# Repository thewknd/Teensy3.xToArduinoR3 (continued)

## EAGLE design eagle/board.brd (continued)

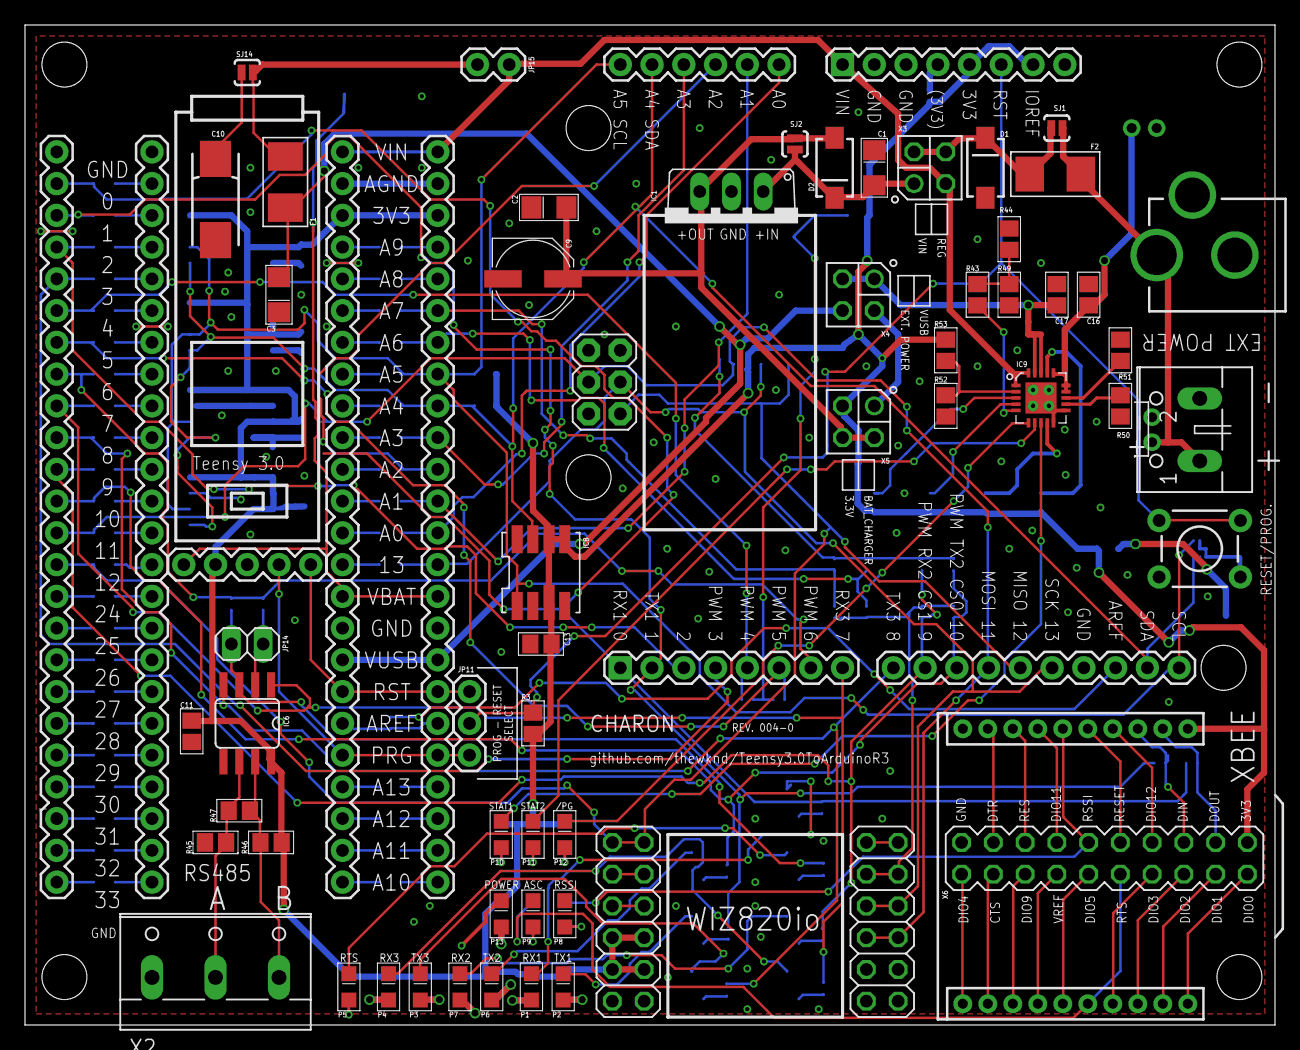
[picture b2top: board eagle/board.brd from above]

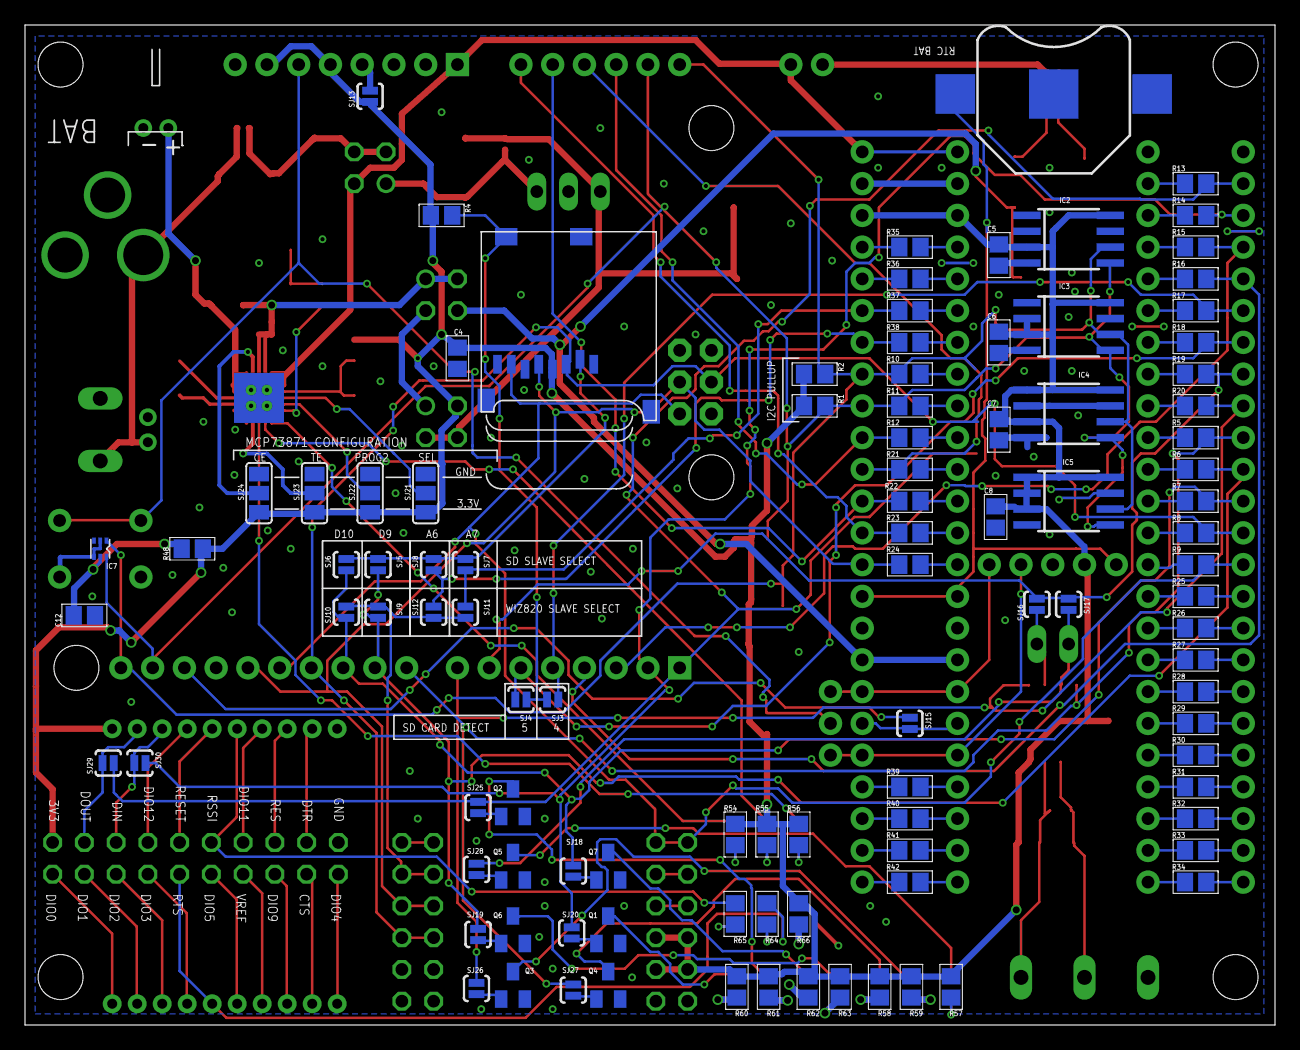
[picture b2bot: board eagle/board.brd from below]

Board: 2 copper layers, 100.0 x 80.0 mm, 174 parts (103 on the bottom side), 165 nets.

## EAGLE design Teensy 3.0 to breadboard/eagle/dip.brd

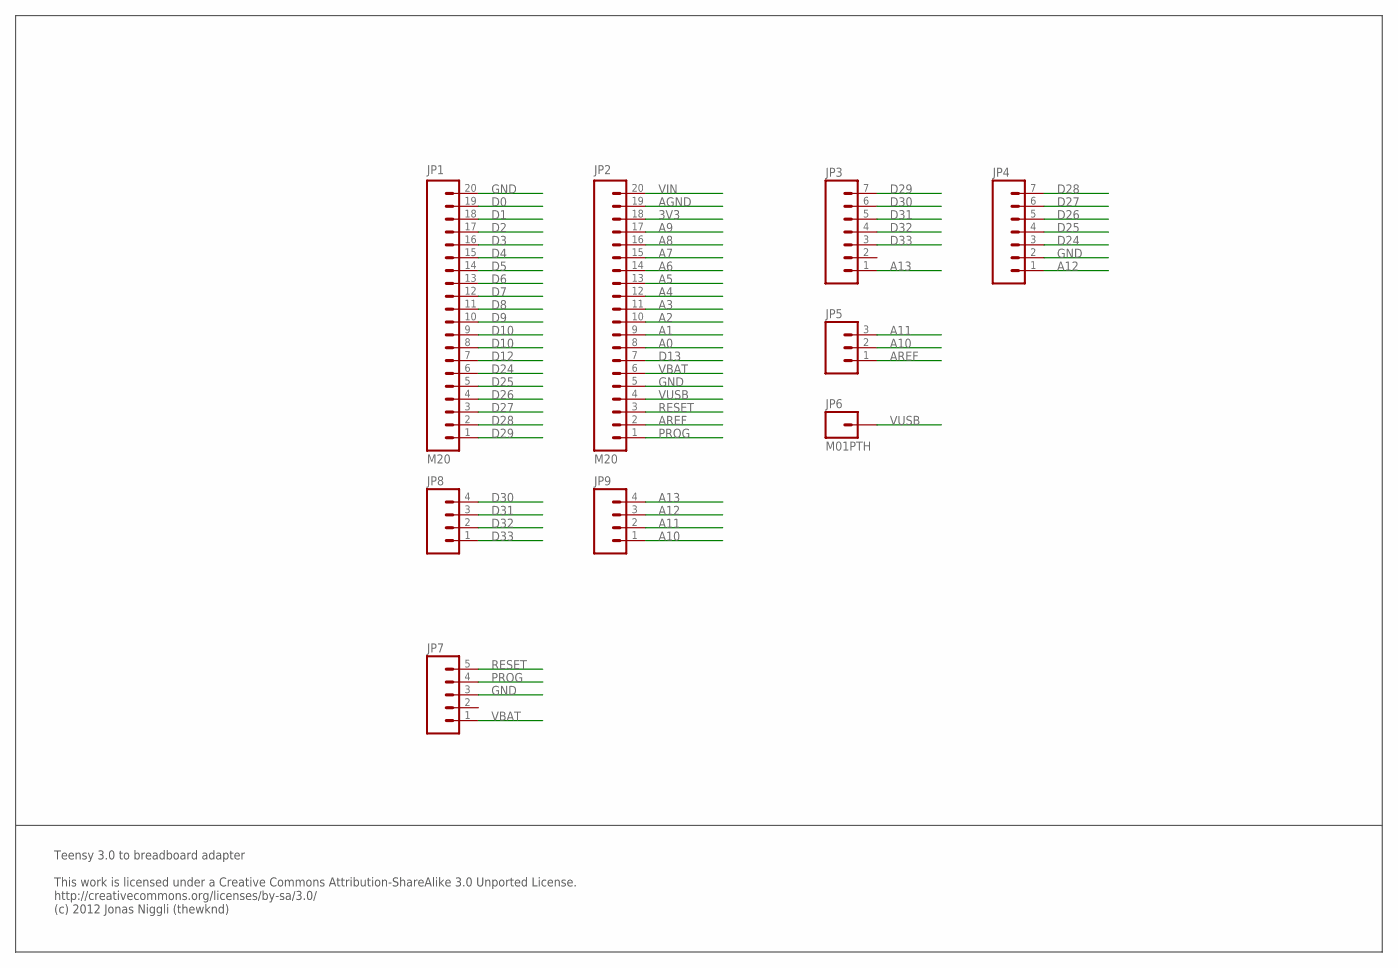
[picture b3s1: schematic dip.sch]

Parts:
JP1, JP2: M20; 1X20
JP3, JP4: M07; 1X07
JP5: M03PTH; 1X03
JP6: M01PTH; 1X01
JP7: M05PTH; 1X05
JP8, JP9: M04PTH; 1X04

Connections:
3V3: JP2.18
A0: JP2.8
A1: JP2.9
A2: JP2.10
A3: JP2.11
A4: JP2.12
A5: JP2.13
A6: JP2.14
A7: JP2.15
A8: JP2.16
A9: JP2.17
A10: JP5.2, JP9.1
A11: JP5.3, JP9.2
A12: JP4.1, JP9.3
A13: JP3.1, JP9.4
AGND: JP2.19
AREF: JP2.2, JP5.1
D0: JP1.19
D1: JP1.18
D2: JP1.17
D3: JP1.16
D4: JP1.15
D5: JP1.14
D6: JP1.13
D7: JP1.12
D8: JP1.11
D9: JP1.10
D10: JP1.9
D11: JP1.8
D12: JP1.7
D13: JP2.7
D24: JP1.6, JP4.3
D25: JP1.5, JP4.4
D26: JP1.4, JP4.5
D27: JP1.3, JP4.6
D28: JP1.2, JP4.7
D29: JP1.1, JP3.7
D30: JP3.6, JP8.4
D31: JP3.5, JP8.3
D32: JP3.4, JP8.2
D33: JP3.3, JP8.1
GND: JP1.20, JP2.5, JP4.2, JP7.3
PROG: JP2.1, JP7.4
RESET: JP2.3, JP7.5
VBAT: JP2.6, JP7.1
VIN: JP2.20
VUSB: JP2.4, JP6.1

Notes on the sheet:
Teensy 3.0 to breadboard adapter This work is licensed under a Creative Commons Attribution-ShareAlike 3.0 Unported License. http://creativecommons.org/licenses/by-sa/3.0/ (c) 2012 Jonas Niggli (thewknd)

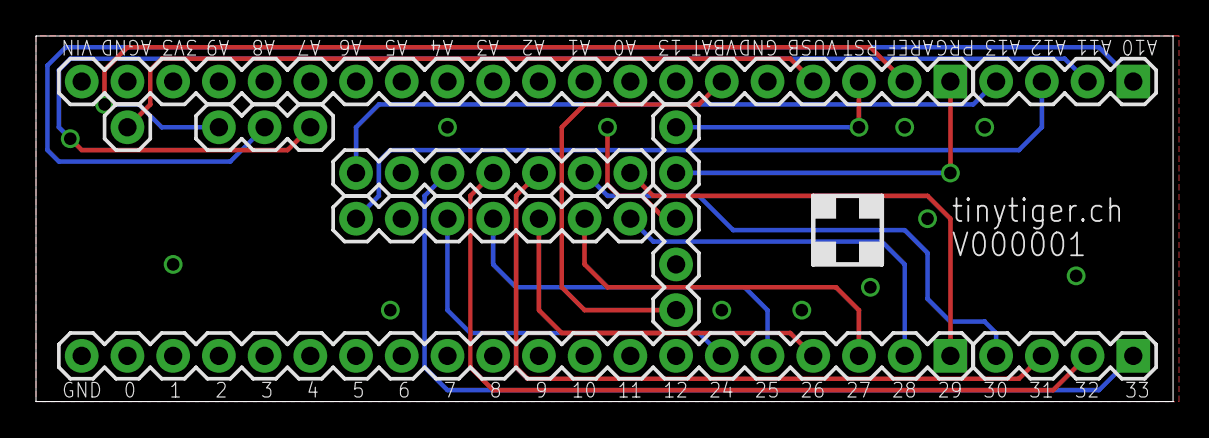
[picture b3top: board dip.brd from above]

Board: 2 copper layers, 63.2 x 20.3 mm, 9 parts (0 on the bottom side), 20 nets.

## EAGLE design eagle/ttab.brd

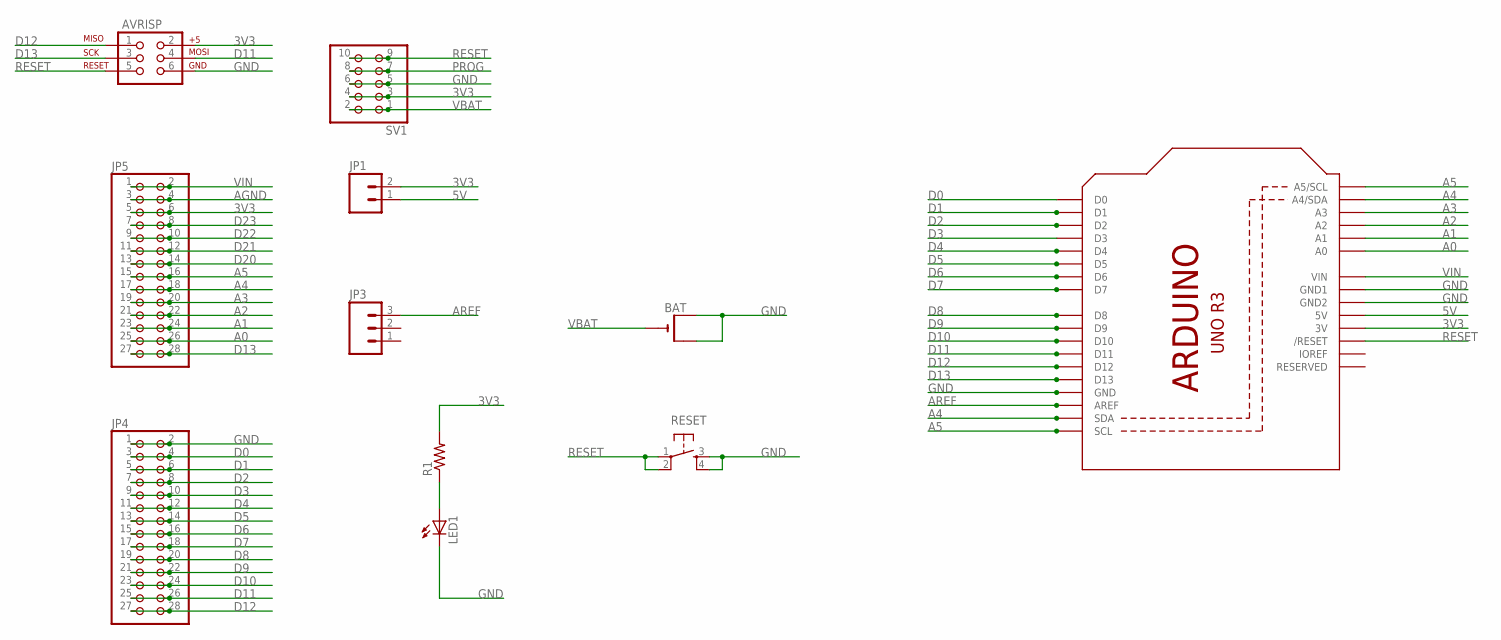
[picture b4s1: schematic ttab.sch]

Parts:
AVRISP: AVR_SPI_PRG_6PTH; 2X3
BAT: CR1220THM; CR1220-THM
JP1: M02LOCK; 1X02_LOCK
JP3: M03PTH; 1X03
JP4, JP5: PINHD-2X14; 2X14
LED1: LEDCHIP-LED0805; CHIP-LED0805
R1: RESISTOR0805-RES; 0805
RESET: TAC_SWITCHPTH; TACTILE-PTH
SV1: PINHD-2X5; 2X05
U4: ARDUINOR3-DIMENSION; ARDUINOR3

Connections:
3V3: AVRISP.2, JP1.2, JP5.5, JP5.6, R1.2, SV1.3, SV1.4, U4.3V
5V: JP1.1, U4.5V
A0: JP5.25, JP5.26, U4.A0
A1: JP5.23, JP5.24, U4.A1
A2: JP5.21, JP5.22, U4.A2
A3: JP5.19, JP5.20, U4.A3
A4: JP5.17, JP5.18, U4.A4 (A4/SDA), U4.SDA
A5: JP5.15, JP5.16, U4.A5 (A5/SCL), U4.SCL
AGND: JP5.3, JP5.4
AREF: JP3.3, U4.AREF
D0: JP4.3, JP4.4, U4.D0
D1: JP4.5, JP4.6, U4.D1
D2: JP4.7, JP4.8, U4.D2
D3: JP4.9, JP4.10, U4.D3
D4: JP4.11, JP4.12, U4.D4
D5: JP4.13, JP4.14, U4.D5
D6: JP4.15, JP4.16, U4.D6
D7: JP4.17, JP4.18, U4.D7
D8: JP4.19, JP4.20, U4.D8
D9: JP4.21, JP4.22, U4.D9
D10: JP4.23, JP4.24, U4.D10
D11: AVRISP.4, JP4.25, JP4.26, U4.D11
D12: AVRISP.1, JP4.27, JP4.28, U4.D12
D13: AVRISP.3, JP5.27, JP5.28, U4.D13
D20: JP5.13, JP5.14
D21: JP5.11, JP5.12
D22: JP5.9, JP5.10
D23: JP5.7, JP5.8
GND: AVRISP.6, BAT.+1 (+), BAT.+2 (+1), JP4.1, JP4.2, LED1.C, RESET.3, RESET.4, SV1.5, SV1.6, U4.GND, U4.GND1, U4.GND2
unnamed: LED1.A, R1.1
PROG: SV1.7, SV1.8
RESET: AVRISP.5, RESET.1, RESET.2, SV1.9, SV1.10, U4.RESET (/RESET)
VBAT: BAT.-, SV1.1, SV1.2
VIN: JP5.1, JP5.2, U4.VIN

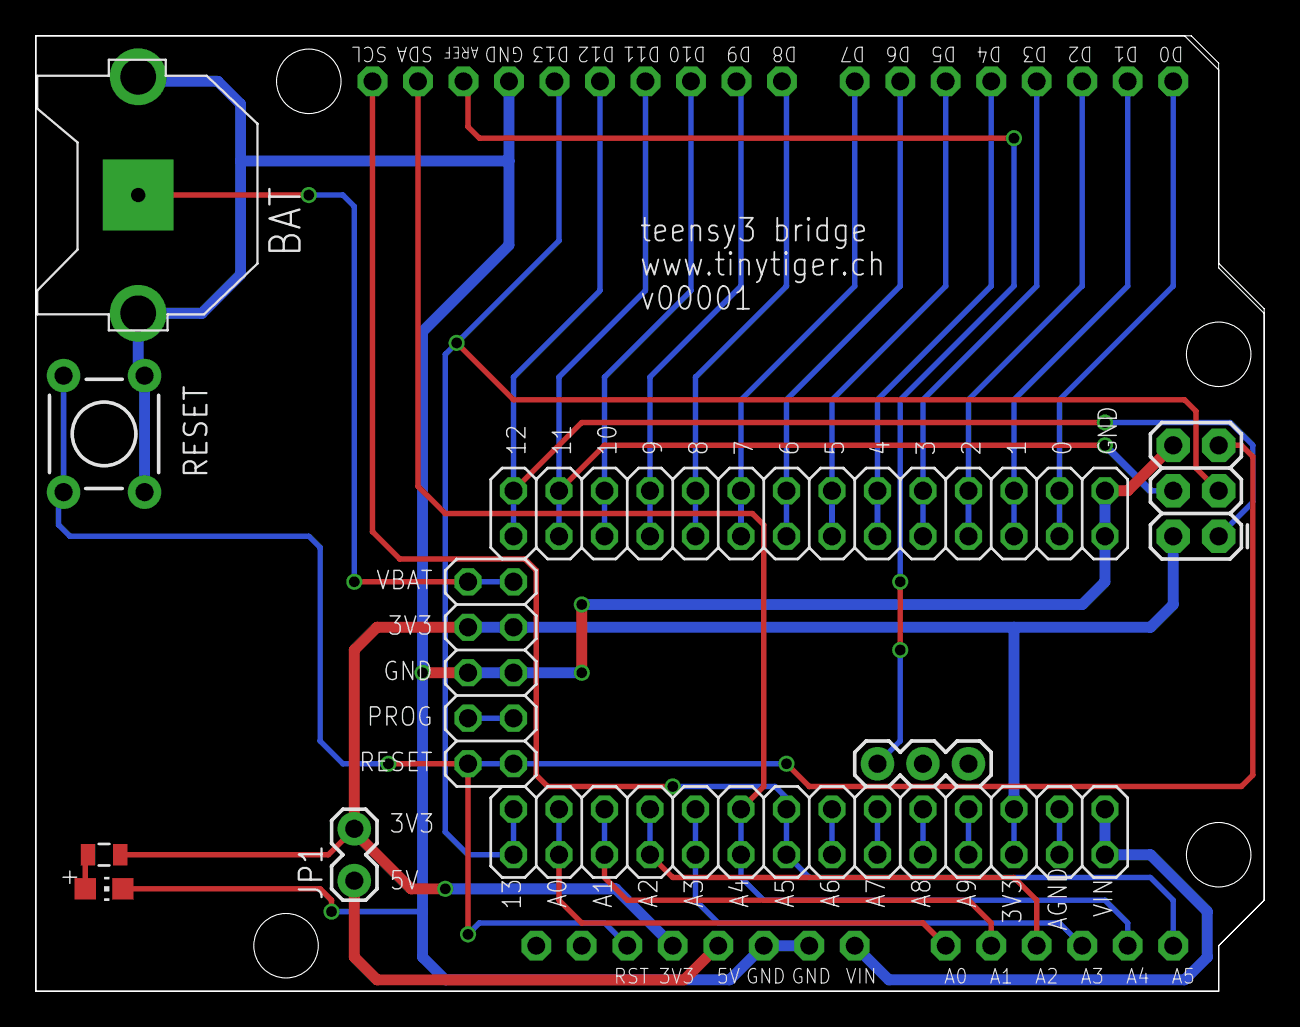
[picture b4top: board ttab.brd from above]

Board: 2 copper layers, 68.6 x 53.3 mm, 11 parts (0 on the bottom side), 34 nets.

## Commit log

2012-11-18 added readme
2012-11-20 new board
    new board: teensy 3.0 to breadboard adapter
2012-11-20 update breadboard adapter
2012-11-21 new teensy 3.0 to arduino R3 board
2012-11-22 update Arduino R3 board
2012-11-24 update: -Arduino R3 pcb - breadboard pcb
2012-11-24 added i2c eeprom, sdcard
2012-11-28 update description
2012-12-08 Version 3 final
2012-12-19 V3-2: fixed several bugs
2013-01-04 inital commit V4
2013-01-06 -added RS485 transceiver
2013-01-13 added Li Battery Charger, variometer, temperature sensor
2013-01-13 clean up
2013-08-05 inital commit for V5
2013-08-05 new 3d images
2013-08-07 upload BOM
2013-09-07 update design
